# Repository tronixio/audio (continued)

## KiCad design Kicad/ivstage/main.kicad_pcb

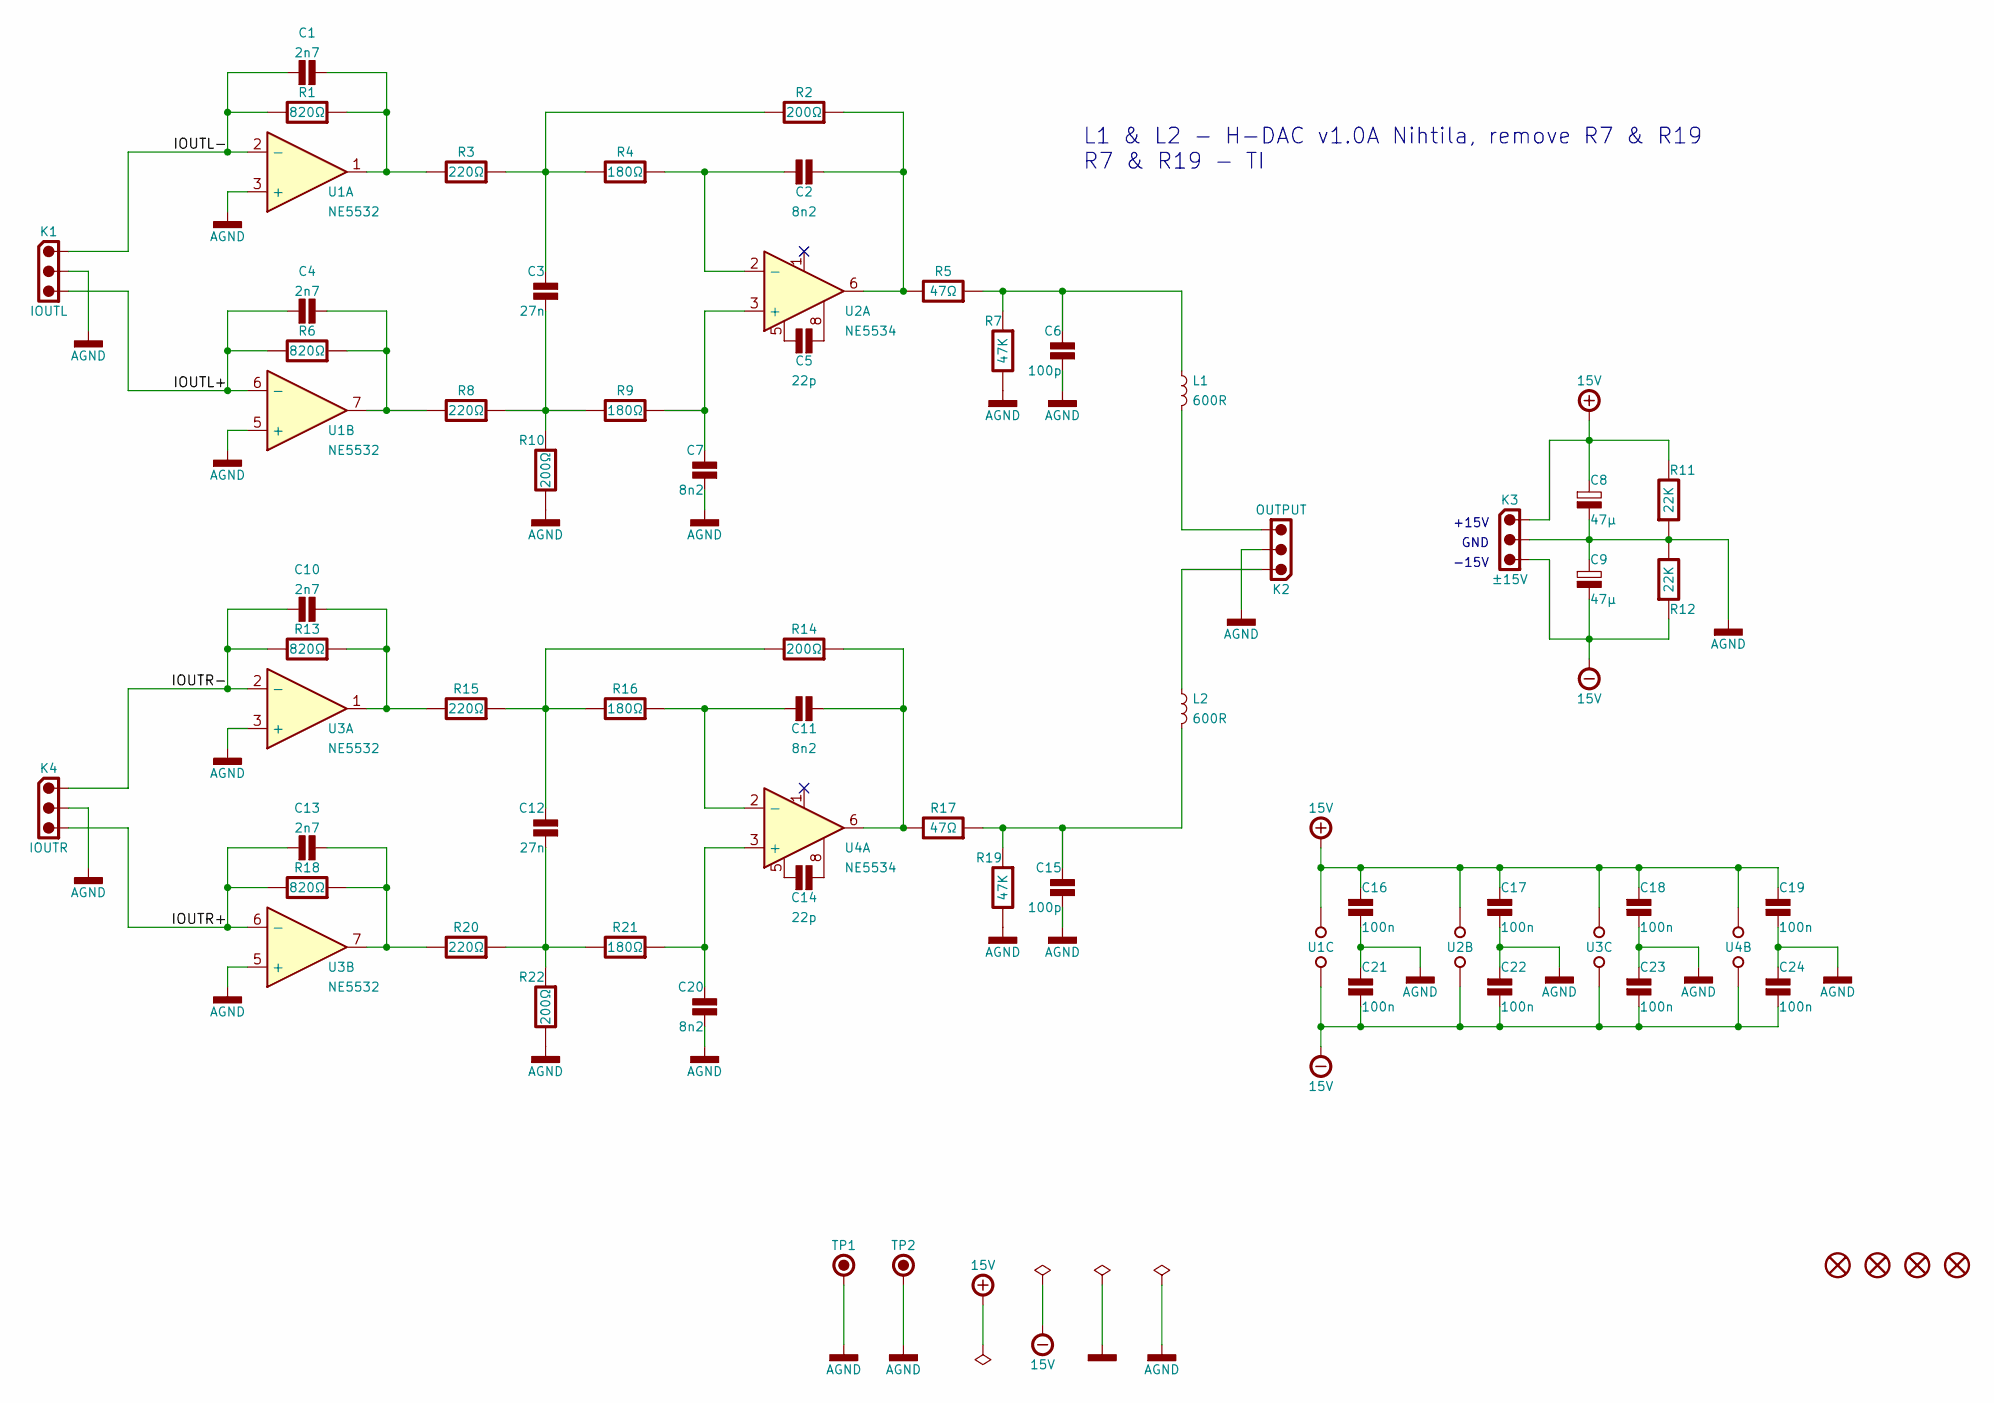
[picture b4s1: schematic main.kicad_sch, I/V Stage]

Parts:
C1, C4, C10, C13: 2n7; CAPACITOR-SMD-1206; Voltage 100V; Tolerance 1%; Mouser 581-12061A101F
C2, C7, C11, C20: 8n2; CAPACITOR-SMD-1206; Voltage 100V; Tolerance 5%; Mouser 581-12061A220JAT4A
C3, C12: 27n; CAPACITOR-SMD-1206; Voltage 100V; Tolerance 1%; Mouser 581-12061A101F
C5, C14: 22p; CAPACITOR-SMD-1206; Voltage 100V; Tolerance 5%; Mouser 581-12061A220JAT4A
C6, C15: 100p; CAPACITOR-SMD-1206; Voltage 100V; Tolerance 1%; Mouser 581-12061A101F
C8, C9: 47µ; CAPACITOR-ELECTROLYTIC-RADIAL-050-110-020-WURTH; Tolerance 20%; Voltage 35V; Mouser 710-860010572005
C16, C17, C18, C19, C21, C22, C23, C24: 100n; CAPACITOR-SMD-1206; Voltage 50V; Tolerance 20%; Mouser 80-C1206C105M5R
H1, H2, H3, H4: MOUNTING-HOLE-3MM-MASK
K1: IOUTL; MOLEX-532530370; Mouser 538-53253-0370
K2: OUTPUT; MOLEX-532530370; Mouser 538-53253-0370
K3: ±15V; MOLEX-532580329; Mouser 538-53258-0329
K4: IOUTR; MOLEX-532530370; Mouser 538-53253-0370
L1, L2: 600R; INDUCTOR-SMD-0805; Mouser 710-742792040
R1, R6, R13, R18: 820Ω; RESISTOR-SMD-1206; Tolerance 1%; Mouser 603-RT1206FRE13820RL
R2, R10, R14, R22: 200Ω; RESISTOR-SMD-1206; Tolerance 1%; Mouser 603-RT1206FRE13200RL
R3, R8, R15, R20: 220Ω; RESISTOR-SMD-1206; Tolerance 1%; Mouser 603-RT1206FRE13220RL
R4, R9, R16, R21: 180Ω; RESISTOR-SMD-1206; Tolerance 1%; Mouser 603-RT1206FRE07180RL
R5, R17: 47Ω; RESISTOR-SMD-1206; Tolerance 1%; Mouser 603-RT1206FRE1310KL
R7, R19: 47K; RESISTOR-SMD-1206; Tolerance 1%; Mouser 603-RT1206FRE1347KL
R11, R12: 22K; RESISTOR-SMD-1206; Tolerance 5%; Mouser 660-RK73B2BTTDD223J
TP1, TP2: GND; KEYSTONE-5006; Mouser 534-5006
U1, U3: NE5532; DIP-08-W762; Mouser 595-NE5532P
U2, U4: NE5534; DIP-08-W762; Mouser 595-NE5534AP

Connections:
+15V: C8.1, C16.1, C17.1, C18.1, C19.1, K3.1, R11.1, U1.4 (VDD-), U2.7 (VDD+), U3.4 (VDD-), U4.7 (VDD+)
-15V: C9.2, C21.2, C22.2, C23.2, C24.2, K3.3, R12.2, U1.8 (VDD+), U2.4 (VDD-), U3.8 (VDD+), U4.4 (VDD-)
/IOUTL+: C4.1, K1.3, R6.1, U1.6 (-)
/IOUTL-: C1.1, K1.1, R1.1, U1.2 (-)
/IOUTR+: C13.1, K4.3, R18.1, U3.6 (-)
/IOUTR-: C10.1, K4.1, R13.1, U3.2 (-)
AGND: C6.1, C7.1, C8.2, C9.1, C15.1, C16.2, C17.2, C18.2, C19.2, C20.1, C21.1, C22.1, C23.1, C24.1, K1.2, K2.2, K3.2, K4.2, R7.1, R10.1, R11.2, R12.1, R19.1, R22.1, TP1.1, TP2.1, U1.3 (+), U1.5 (+), U3.3 (+), U3.5 (+)
unnamed: C1.2, R1.2, R3.1, U1.1
unnamed: C2.1, R4.2, U2.2 (-)
unnamed: C2.2, R2.2, R5.1, U2.6
unnamed: C3.1, R8.2, R9.1, R10.2
unnamed: C3.2, R2.1, R3.2, R4.1
unnamed: C4.2, R6.2, R8.1, U1.7
unnamed: C5.1, U2.5
unnamed: C5.2, U2.8
unnamed: C6.2, L1.2, R5.2, R7.2
unnamed: C7.2, R9.2, U2.3 (+)
unnamed: C10.2, R13.2, R15.1, U3.1
unnamed: C11.1, R16.2, U4.2 (-)
unnamed: C11.2, R14.2, R17.1, U4.6
unnamed: C12.1, R20.2, R21.1, R22.2
unnamed: C12.2, R14.1, R15.2, R16.1
unnamed: C13.2, R18.2, R20.1, U3.7
unnamed: C14.1, U4.5
unnamed: C14.2, U4.8
unnamed: C15.2, L2.1, R17.2, R19.2
unnamed: C20.2, R21.2, U4.3 (+)
unnamed: K2.1, L2.2
unnamed: K2.3, L1.1

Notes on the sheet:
GND
L1 & L2 - H-DAC v1.0A Nihtila, remove R7 & R19 R7 & R19 - TI
-15V
+15V

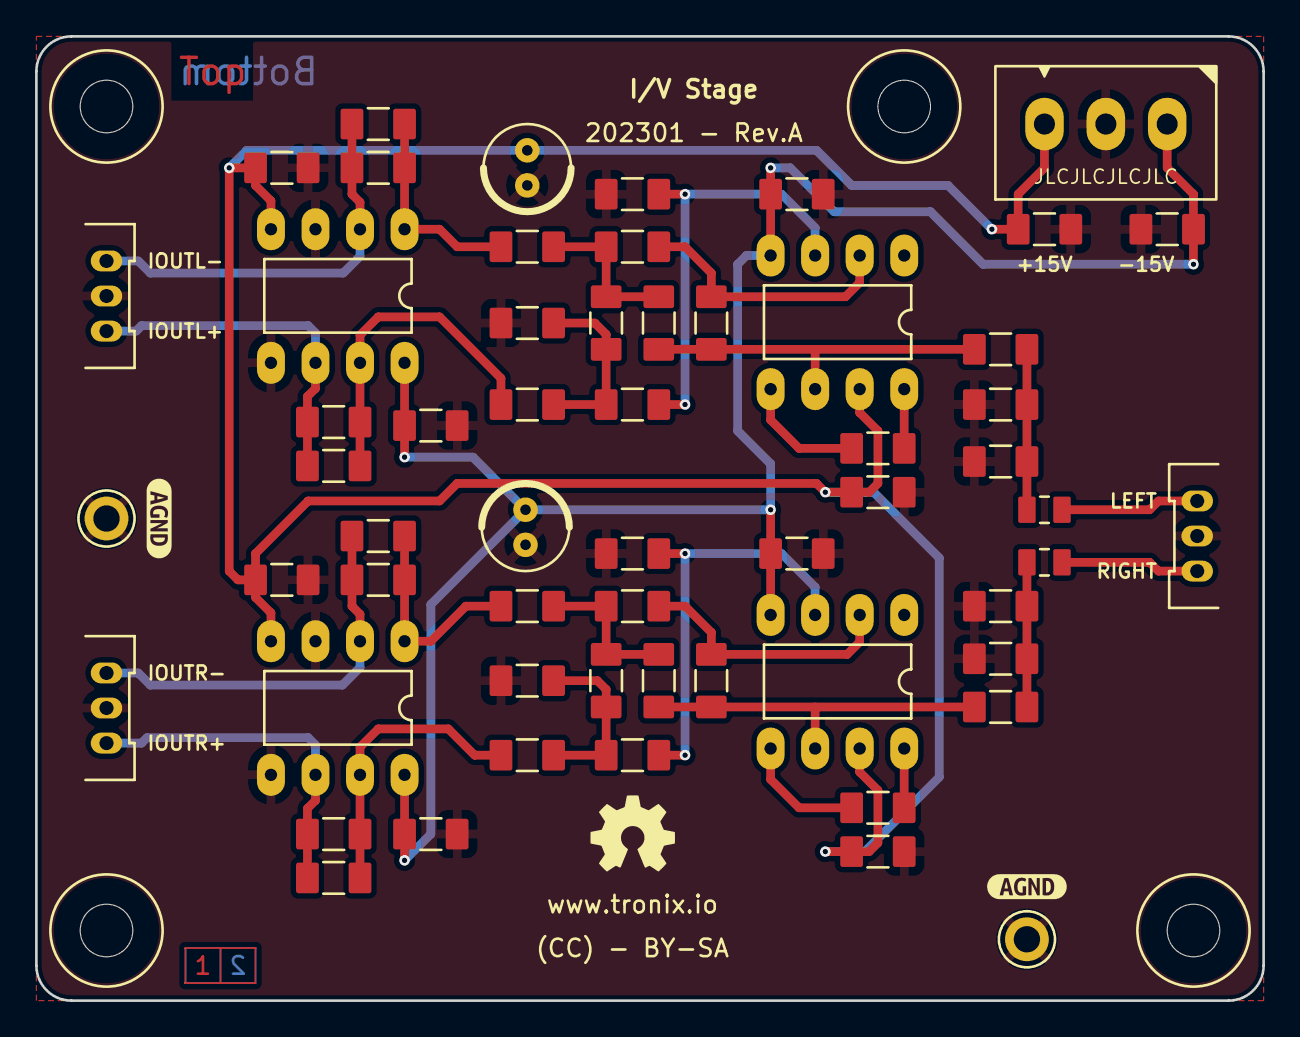
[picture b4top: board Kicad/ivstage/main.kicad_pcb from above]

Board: 2 copper layers, 70.0 x 55.0 mm, 64 parts (0 on the bottom side), 29 nets.

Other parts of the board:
kibuzzard-63CBEF50, kibuzzard-63CBEF50#2: G***; kibuzzard-63CBEF50

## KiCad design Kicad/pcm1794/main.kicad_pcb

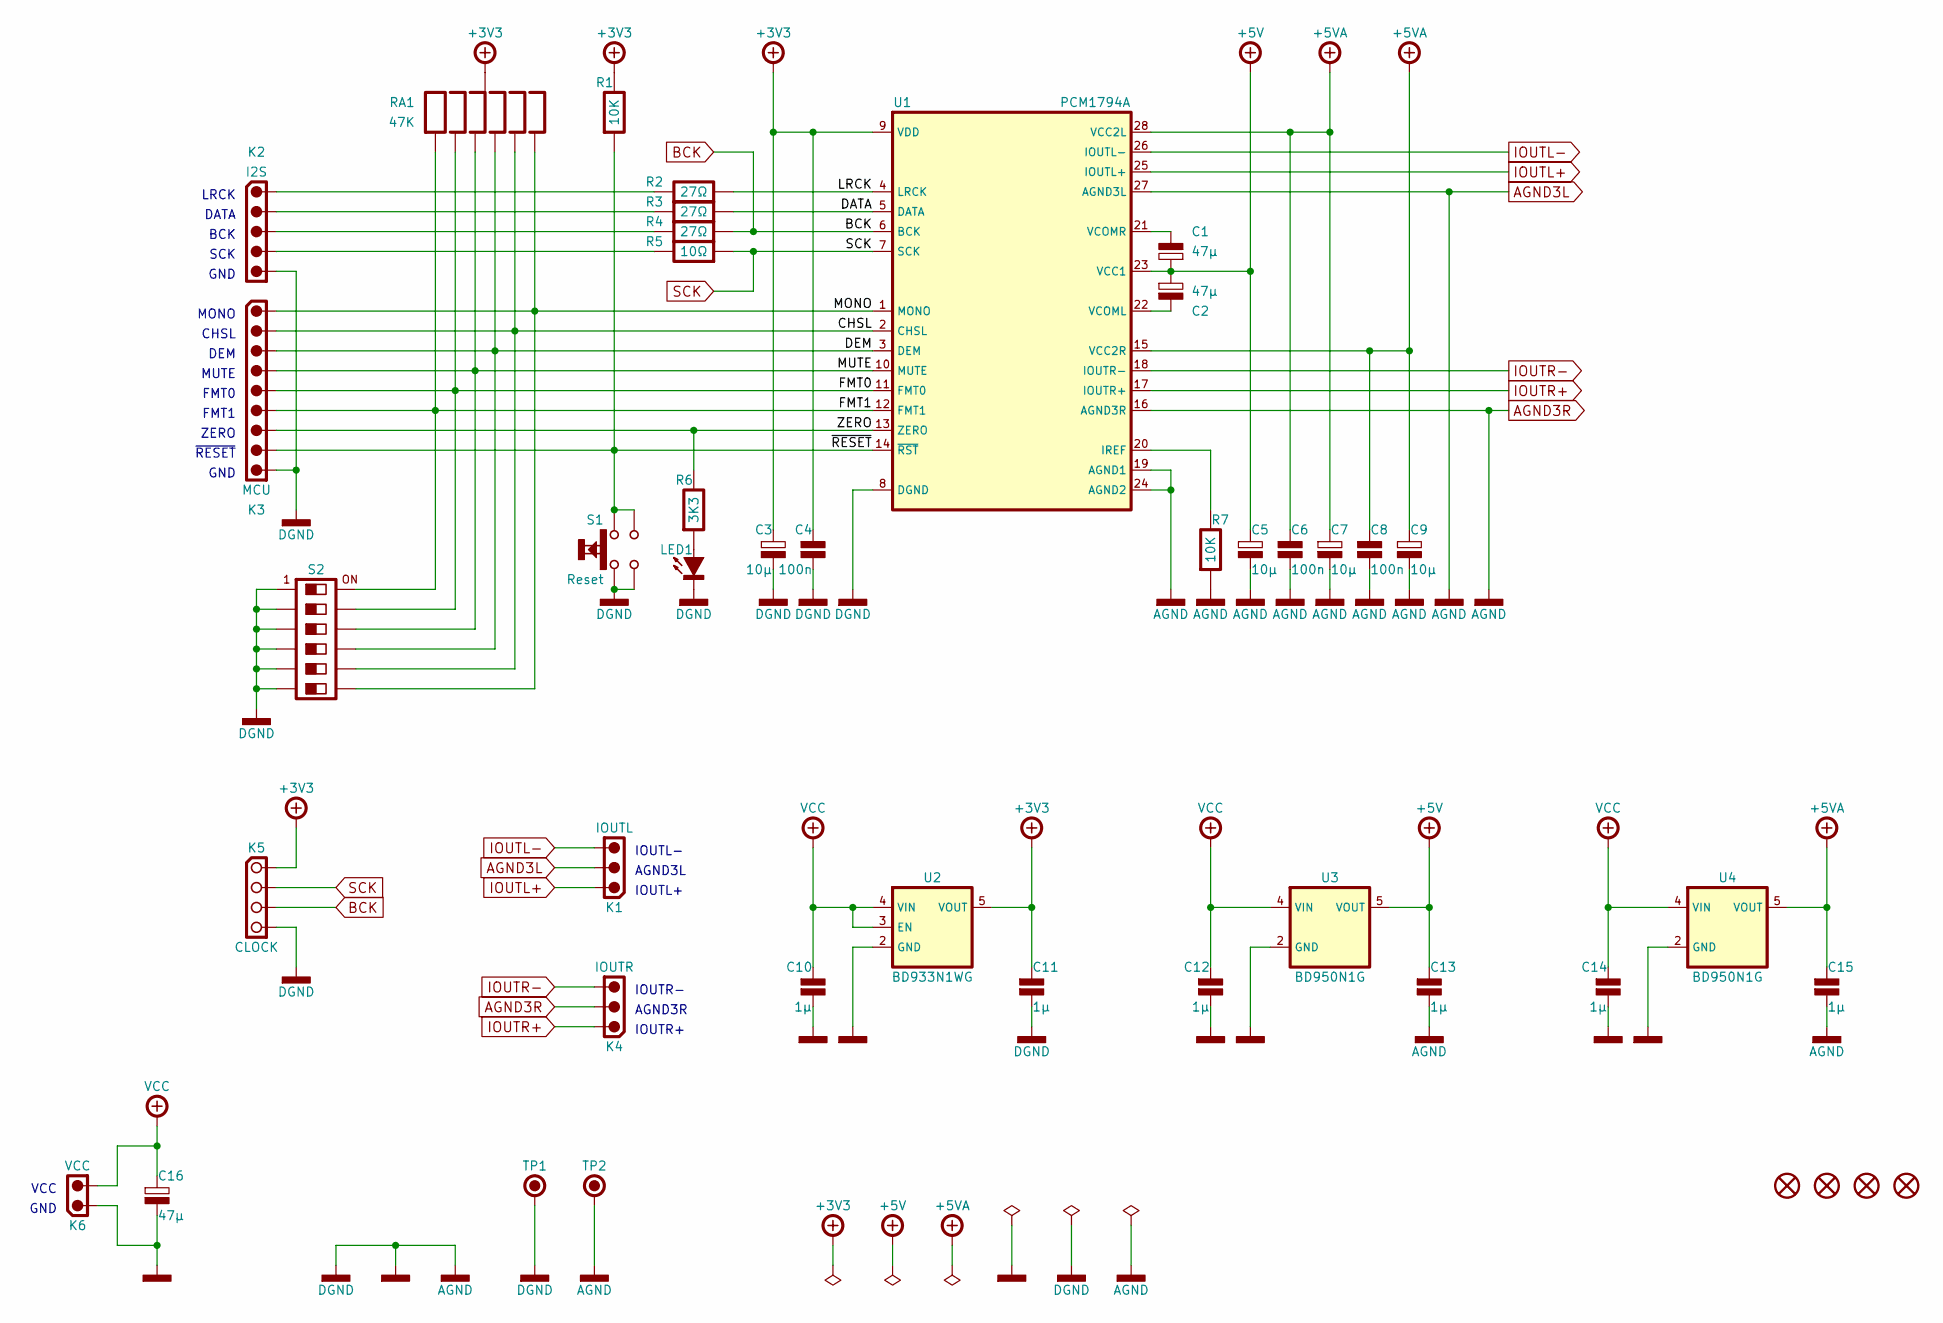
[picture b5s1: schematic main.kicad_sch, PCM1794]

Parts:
C1, C2, C16: 47µ; CAPACITOR-ELECTROLYTIC-RADIAL-050-110-020-WURTH; Tolerance 20%; Voltage 35V; Mouser 710-860010572005
C3, C5, C7, C9: 10µ; CAPACITOR-ELECTROLYTIC-RADIAL-050-110-020-WURTH; Tolerance 20%; Voltage 63V; Mouser 710-860010772009
C4, C6, C8: 100n; CAPACITOR-SMD-1206; Voltage 50V; Tolerance 20%; Mouser 80-C1206C105M5R
C10, C11, C12, C13, C14, C15: 1µ; CAPACITOR-SMD-1206; Voltage 50V; Tolerance 20%; Mouser 80-C1206C105M5R
H1, H2, H3, H4: MOUNTING-HOLE-3MM-MASK
K1: IOUTL; MOLEX-532530370; Mouser 538-53253-0370
K2: I2S; MOLEX-532530570; Mouser 538-53253-0570
K3: MCU; HARWIN-M20-999094x; Mouser 855-M20-999094
K4: IOUTR; MOLEX-532530370; Mouser 538-53253-0370
K5: CLOCK; HARWIN-M20-782044x; Mouser 855-M20-782044
K6: VCC; MOLEX-532580229; Mouser 538-53258-0229
LED1: KINGBRIGHT-LED-1206-RED; LED-SMD-1206; Mouser 604-APT3216LSECKJ3RV
R1: 10K; RESISTOR-SMD-1206; Tolerance 5%; Mouser 660-RK73B2BTTDD103J
R2, R3, R4: 27Ω; RESISTOR-SMD-1206; Tolerance 1%; Mouser 603-RT1206FRE0727RL
R5: 10Ω; RESISTOR-SMD-1206; Tolerance 1%; Mouser 603-RT1206FRE1310RL
R6: 3K3; RESISTOR-SMD-1206; Tolerance 5%; Mouser 660-RK73B2BTTDD332J
R7: 10K; RESISTOR-SMD-1206; Tolerance 1%; Mouser 603-RT1206FRE1310KL
RA1: 47K; BOURNS-4607X; Tolerance 2%; Mouser 652-4607X-1LF-47K
S1: Reset; ALPS-SKRPAC; Mouser 688-SKRPACE010
S2: CUI-DS01-254-06; DIP-SWITCH-06-W762; Mouser 490-DS04-254-1L-06BK
TP1, TP2: GND; KEYSTONE-5006; Mouser 534-5006
U1: PCM1794A; SSOP-28; Mouser 595-PCM1794ADBR
U2: BD933N1WG; SOT-23-5; Mouser 755-BD933N1WG-CTR
U3, U4: BD950N1G; SOT-23-5; Mouser 755-BD950N1G-CTR

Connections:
+3V3: C3.1, C4.1, C11.1, K5.1, R1.1, RA1.1, U1.9 (VDD), U2.5 (VOUT)
+5V: C1.1, C2.1, C5.1, C13.1, U1.23 (VCC1), U3.5 (VOUT)
+5VA: C6.1, C7.1, C8.1, C9.1, C15.1, U1.15 (VCC2R), U1.28 (VCC2L), U4.5 (VOUT)
/CHSL: K3.2, RA1.6, S2.8, U1.2 (CHSL)
/DATA: R3.2, U1.5 (DATA)
/DEM: K3.3, RA1.5, S2.9, U1.3 (DEM)
/FMT0: K3.5, RA1.3, S2.11, U1.11 (FMT0)
/FMT1: K3.6, RA1.2, S2.12, U1.12 (FMT1)
/LRCK: R2.2, U1.4 (LRCK)
/MONO: K3.1, RA1.7, S2.7, U1.1 (MONO)
/MUTE: K3.4, RA1.4, S2.10, U1.10 (MUTE)
/ZERO: K3.7, R6.1, U1.13 (ZERO)
/~RESET: K3.8, R1.2, S1.3, S1.4, U1.14 (~RST)
AGND3L: C3.2, C4.2, C5.2, C6.2, C7.2, C8.2, C9.2, C10.2, C11.2, C12.2, C13.2, C14.2, C15.2, C16.2, K1.2, K2.5, K3.9, K4.2, K5.4, K6.1, LED1.1 (C), R7.2, S1.1, S1.2, S2.1, S2.2, S2.3, S2.4, S2.5, S2.6, TP1.1, TP2.1, U1.8 (DGND), U1.16 (AGND3R), U1.19 (AGND1), U1.24 (AGND2), U1.27 (AGND3L), U2.2 (GND), U3.2 (GND), U4.2 (GND)
BCK: K5.3, R4.2, U1.6 (BCK)
IOUTL+: K1.1, U1.25 (IOUTL+)
IOUTL-: K1.3, U1.26 (IOUTL-)
IOUTR+: K4.1, U1.17 (IOUTR+)
IOUTR-: K4.3, U1.18 (IOUTR-)
unnamed: C1.2, U1.21 (VCOMR)
unnamed: C2.2, U1.22 (VCOML)
unnamed: K2.1, R2.1
unnamed: K2.2, R3.1
unnamed: K2.3, R4.1
unnamed: K2.4, R5.1
unnamed: LED1.2 (A), R6.2
unnamed: R7.1, U1.20 (IREF)
SCK: K5.2, R5.2, U1.7 (SCK)
VCC: C10.1, C12.1, C14.1, C16.1, K6.2, U2.3 (EN), U2.4 (VIN), U3.4 (VIN), U4.4 (VIN)

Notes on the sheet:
IOUTR+
FMT1
GND
AGND3R
ZERO
AGND3L
BCK
LRCK
MONO
~{RESET}
SCK
MUTE
CHSL
VCC
IOUTR-
IOUTL-
FMT0
DEM
IOUTL+
DATA

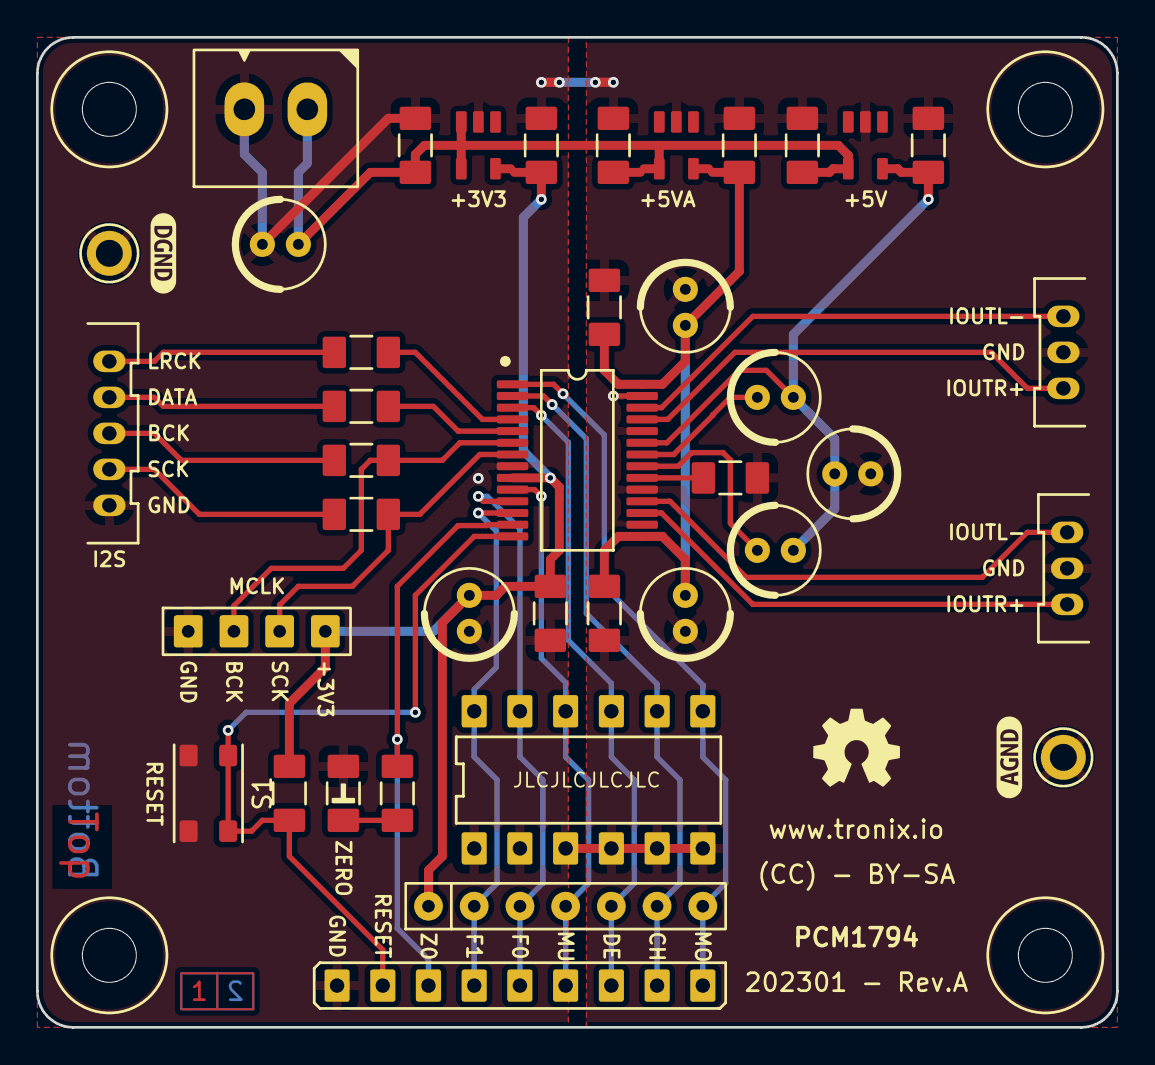
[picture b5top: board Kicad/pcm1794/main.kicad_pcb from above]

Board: 2 copper layers, 60.0 x 55.0 mm, 45 parts (0 on the bottom side), 29 nets.

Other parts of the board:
kibuzzard-63CAF235: G***; kibuzzard-63CAF235
kibuzzard-63CBA350: G***; kibuzzard-63CBA350
